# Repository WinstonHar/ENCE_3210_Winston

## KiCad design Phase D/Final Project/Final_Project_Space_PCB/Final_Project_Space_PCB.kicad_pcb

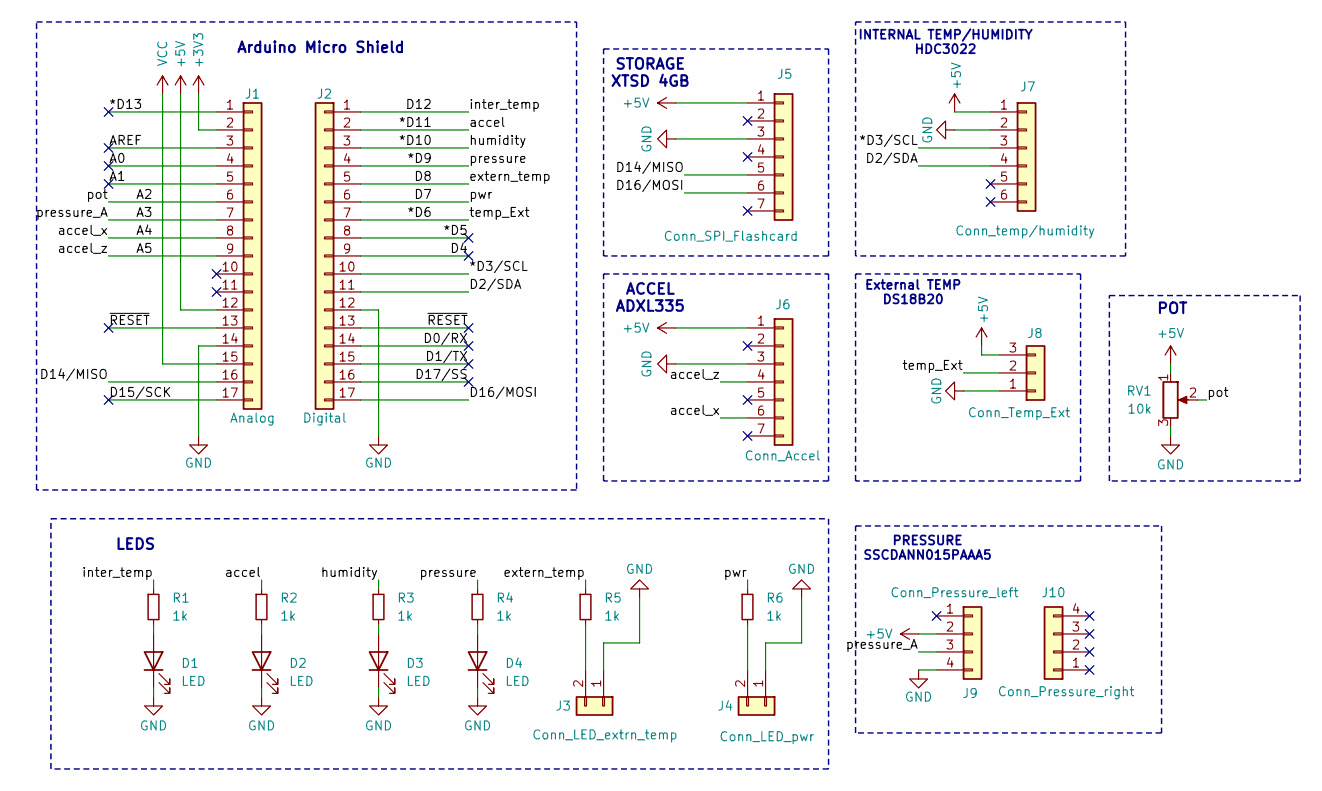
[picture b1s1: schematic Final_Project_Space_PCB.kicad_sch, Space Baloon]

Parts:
D1, D2, D3, D4: LED; LED_D5.0mm
J1: Analog; PinHeader_1x17_P2.54mm_Vertical
J2: Digital; PinHeader_1x17_P2.54mm_Vertical
J3: Conn_LED_extrn_temp; PinSocket_1x02_P2.54mm_Vertical
J4: Conn_LED_pwr; PinSocket_1x02_P2.54mm_Vertical
J5: Conn_SPI_Flashcard; PinSocket_1x07_P2.54mm_Vertical
J6: Conn_Accel; PinSocket_1x07_P2.54mm_Vertical
J7: Conn_temp/humidity; PinSocket_1x06_P2.54mm_Vertical
J8: Conn_Temp_Ext; JST_XH_B3B-XH-A_1x03_P2.50mm_Vertical
J9: Conn_Pressure_left; PinSocket_1x04_P2.54mm_Vertical
J10: Conn_Pressure_right; PinSocket_1x04_P2.54mm_Vertical
R1, R2, R3, R4, R5, R6: 1k; R_Axial_DIN0204_L3.6mm_D1.6mm_P7.62mm_Horizontal
RV1: 10k; Potentiometer_Bourns_3386P_Vertical

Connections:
+3V3: J1.2
+5V: J1.12, J5.1, J6.1, J7.1, J8.3, J9.2, RV1.1
/*D3/SCL: J2.10, J7.3
/*D5: J2.8
/*D6: J2.7, J8.2
/*D9: J2.4, R4.1
/*D10: J2.3, R3.1
/*D11: J2.2, R2.1
/*D13: J1.1
/A0: J1.4
/A1: J1.5
/A2: J1.6, RV1.2
/A3: J1.7, J9.3
/A4: J1.8, J6.6
/A5: J1.9, J6.4
/AREF: J1.3
/D0/RX: J2.14
/D1/TX: J2.15
/D2/SDA: J2.11, J7.4
/D4: J2.9
/D7: J2.6, R6.1
/D8: J2.5, R5.1
/D12: J2.1, R1.1
/D14/MISO: J1.16, J5.5
/D15/SCK: J1.17
/D16/MOSI: J2.17, J5.6
/D17/SS: J2.16
/~RESET: J1.13, J2.13
GND: D1.1 (K), D2.1 (K), D3.1 (K), D4.1 (K), J1.14, J2.12, J3.1, J4.1, J5.3, J6.3, J7.2, J8.1, J9.4, RV1.3
unnamed: D1.2 (A), R1.2
unnamed: D2.2 (A), R2.2
unnamed: D3.2 (A), R3.2
unnamed: D4.2 (A), R4.2
unnamed: J3.2, R5.2
unnamed: J4.2, R6.2
VCC: J1.15

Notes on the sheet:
ACCEL ADXL335
POT
Arduino Micro Shield
LEDS
INTERNAL TEMP/HUMIDITY HDC3022
STORAGE XTSD 4GB
External TEMP DS18B20
PRESSURE SSCDANN015PAAA5

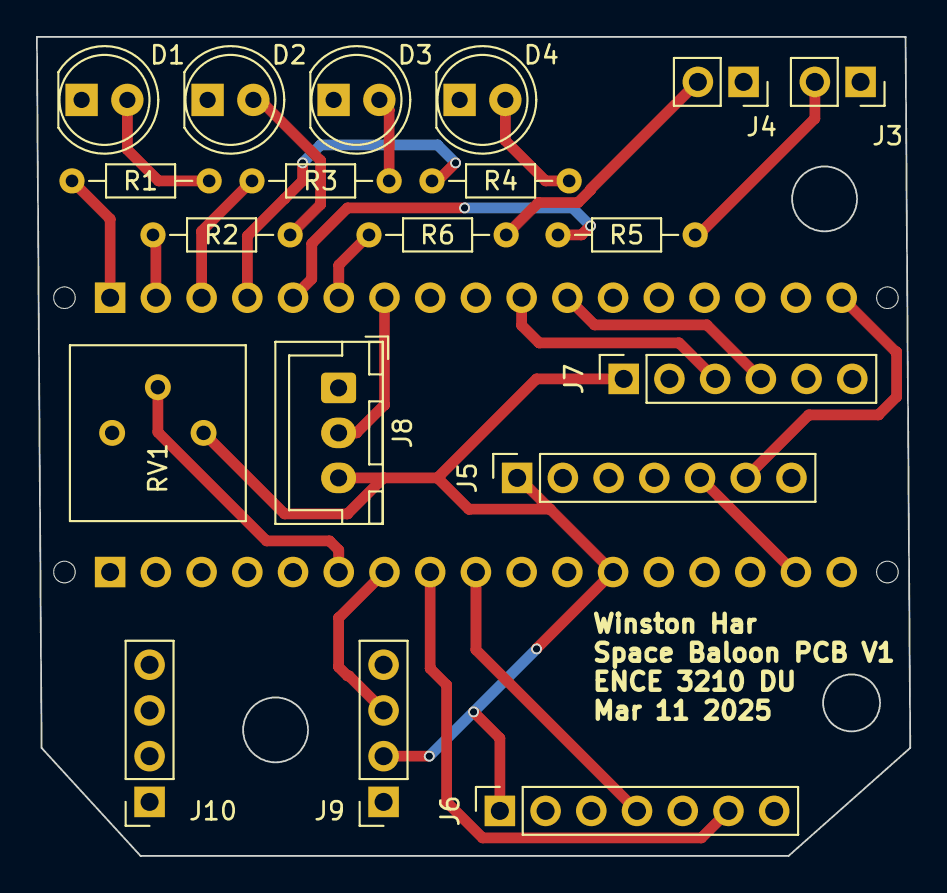
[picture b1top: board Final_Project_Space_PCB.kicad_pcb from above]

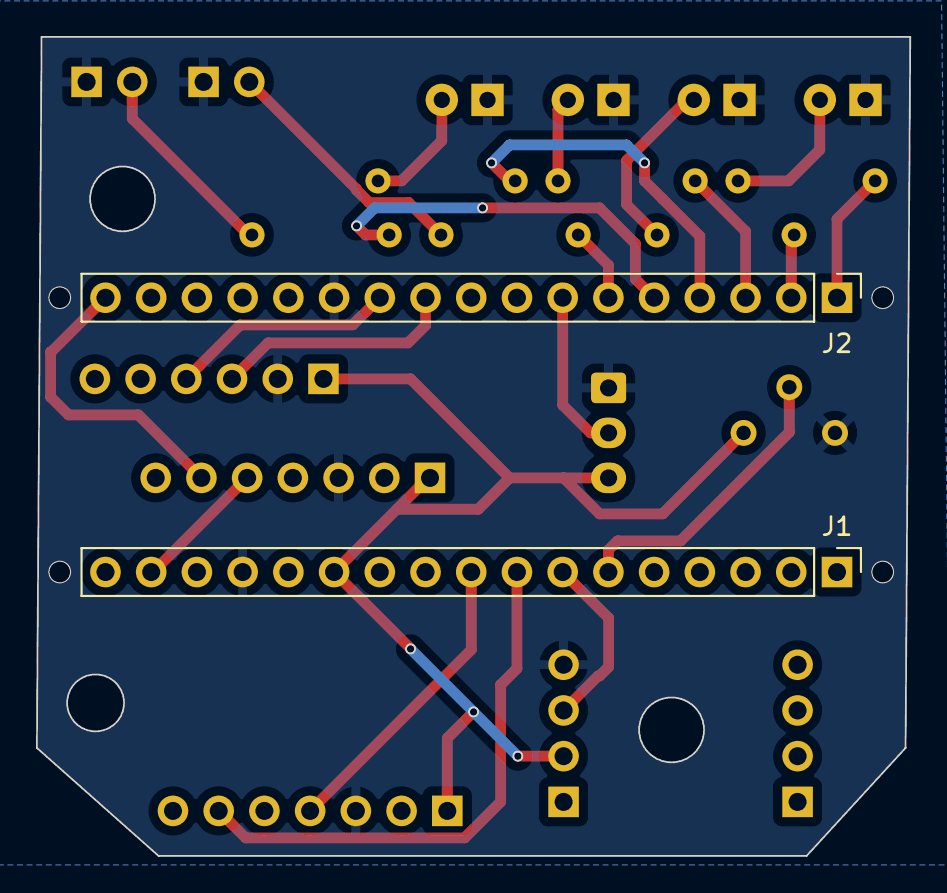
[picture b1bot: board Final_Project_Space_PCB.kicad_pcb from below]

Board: 2 copper layers, 48.5 x 45.5 mm, 25 parts (2 on the bottom side), 24 nets.

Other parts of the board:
MH1, MH2, MH3, MH4: MountingHole_1.2mm

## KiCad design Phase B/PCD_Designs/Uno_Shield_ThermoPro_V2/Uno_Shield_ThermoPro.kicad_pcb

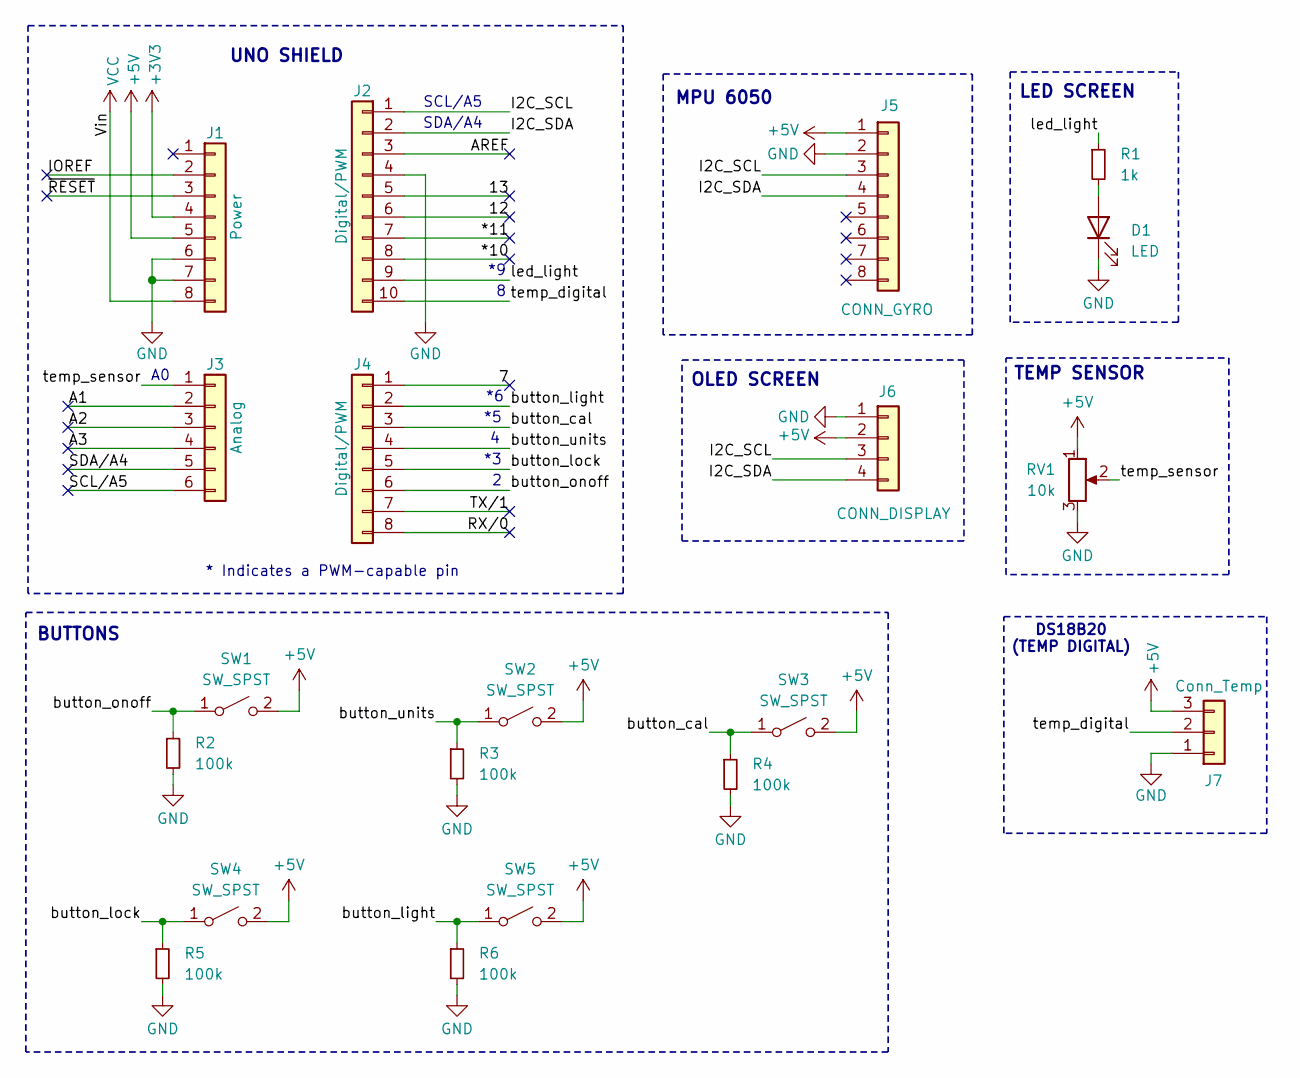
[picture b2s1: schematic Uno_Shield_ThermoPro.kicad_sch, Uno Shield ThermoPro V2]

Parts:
D1: LED; LED_D5.0mm
J1: Power; PinSocket_1x08_P2.54mm_Vertical
J2: Digital/PWM; PinSocket_1x10_P2.54mm_Vertical
J3: Analog; PinSocket_1x06_P2.54mm_Vertical
J4: Digital/PWM; PinSocket_1x08_P2.54mm_Vertical
J5: CONN_GYRO; PinSocket_1x08_P2.54mm_Vertical
J6: CONN_DISPLAY; PinSocket_1x04_P2.54mm_Vertical
J7: Conn_Temp; JST_XH_B3B-XH-A_1x03_P2.50mm_Vertical
R1: 1k; R_Axial_DIN0207_L6.3mm_D2.5mm_P10.16mm_Horizontal
R2, R3, R4, R5, R6: 100k; R_Axial_DIN0207_L6.3mm_D2.5mm_P10.16mm_Horizontal
RV1: 10k; Potentiometer_Bourns_3386P_Vertical
SW1, SW2, SW3, SW4, SW5: SW_SPST; SW_PUSH_6mm

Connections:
+3V3: J1.4
+5V: J1.5, J5.1, J6.2, J7.3, RV1.1, SW1.2 (B), SW2.2 (B), SW3.2 (B), SW4.2 (B), SW5.2 (B)
/7: J4.1
/12: J2.6
/13: J2.5
/*10: J2.8
/*11: J2.7
/A1: J3.2
/A2: J3.3
/A3: J3.4
/AREF: J2.3
/I2C_SCL: J2.1, J5.3, J6.3
/I2C_SDA: J2.2, J5.4, J6.4
/IOREF: J1.2
/RX/0: J4.8
/SCL/A5: J3.6
/SDA/A4: J3.5
/TX/1: J4.7
/button_cal: J4.3, R4.1, SW3.1 (A)
/button_light: J4.2, R6.1, SW5.1 (A)
/button_lock: J4.5, R5.1, SW4.1 (A)
/button_onoff: J4.6, R2.1, SW1.1 (A)
/button_units: J4.4, R3.1, SW2.1 (A)
/led_light: J2.9, R1.1
/temp_digital: J2.10, J7.2
/temp_sensor: J3.1, RV1.2
/~RESET: J1.3
GND: D1.1 (K), J1.6, J1.7, J2.4, J5.2, J6.1, J7.1, R2.2, R3.2, R4.2, R5.2, R6.2, RV1.3
unnamed: D1.2 (A), R1.2
VCC: J1.8

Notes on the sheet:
OLED SCREEN
LED SCREEN
DS18B20 (TEMP DIGITAL)
TEMP SENSOR
UNO SHIELD
MPU 6050
SCL/A5
SDA/A4
BUTTONS
* Indicates a PWM-capable pin

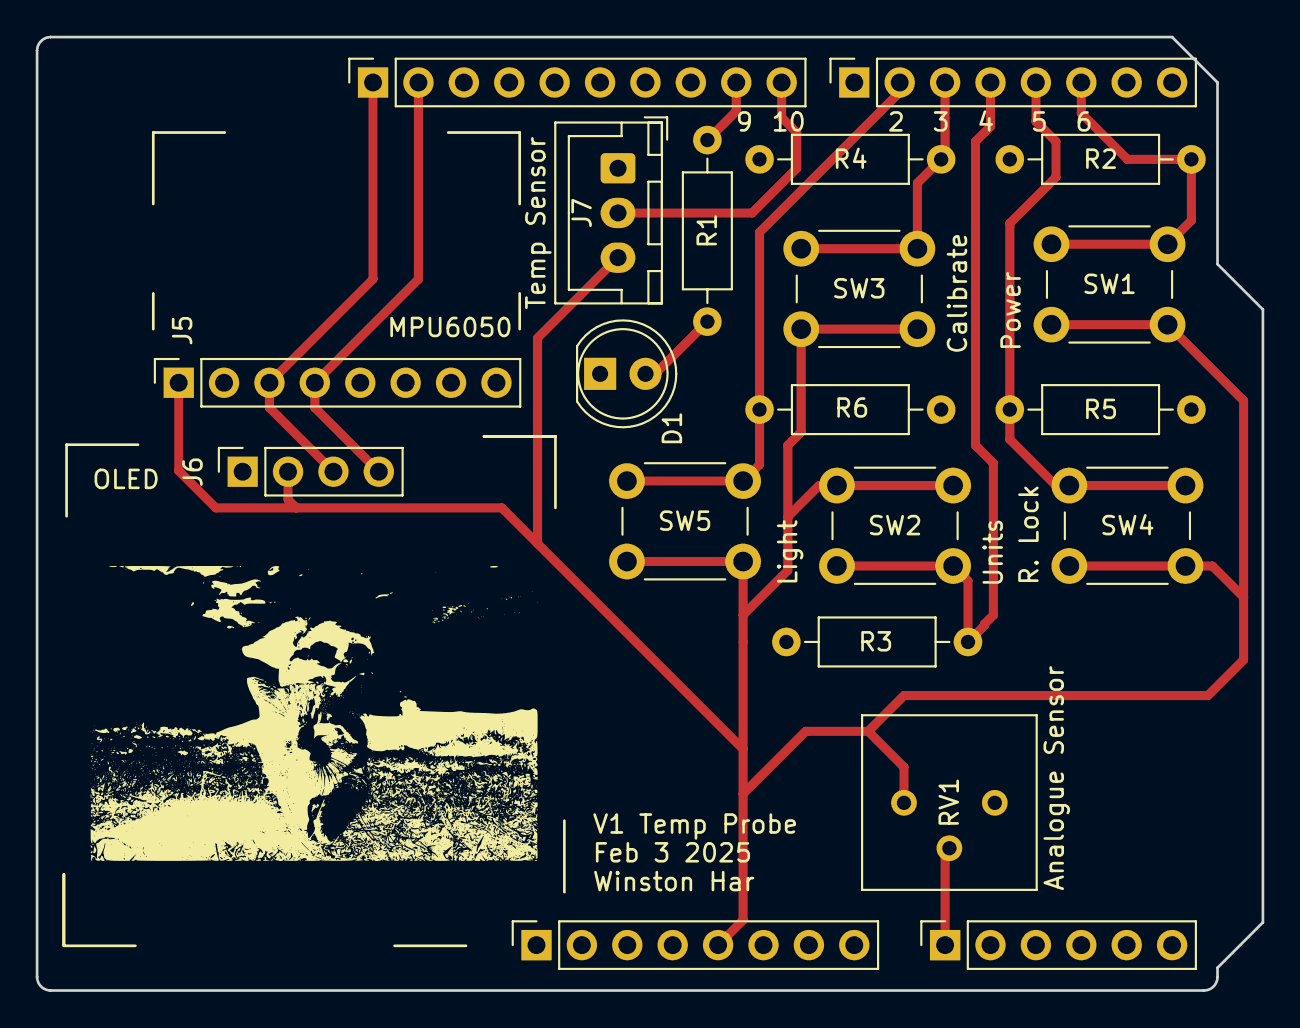
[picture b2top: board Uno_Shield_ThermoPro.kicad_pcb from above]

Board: 2 copper layers, 68.6 x 53.3 mm, 20 parts (0 on the bottom side), 13 nets.

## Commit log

2025-01-10 Create README.md
    Repository for ENGR Class
2025-01-10 Files for lab1, and example
2025-01-10 Adjust location of files
2025-01-13 completed last 3 question (not tested)
2025-01-17 Code for first 3 problems
2025-01-17 Finished question 4
2025-01-24 Lab3 Block Diagram and Code
2025-01-31 Editing layout and first project version upload
2025-02-03 Updated version 2 file
2025-02-03 Updated files in V2 folder, new pdf docs and gerber files
2025-02-03 edit lines
2025-02-04 final
2025-02-04 edit, update gerber
2025-02-04 schematic edits
2025-02-04 edits, final
2025-02-20 Phase C adruino code for temp sensor
2025-02-24 Push lab4 to Phase D
2025-02-25 Added code diagram
2025-03-06 PhotosPt1
2025-03-11 Adding updated calculations and pcb to phase B(will move)
2025-03-12 Added all files for final project
2025-03-13 Added presentation
